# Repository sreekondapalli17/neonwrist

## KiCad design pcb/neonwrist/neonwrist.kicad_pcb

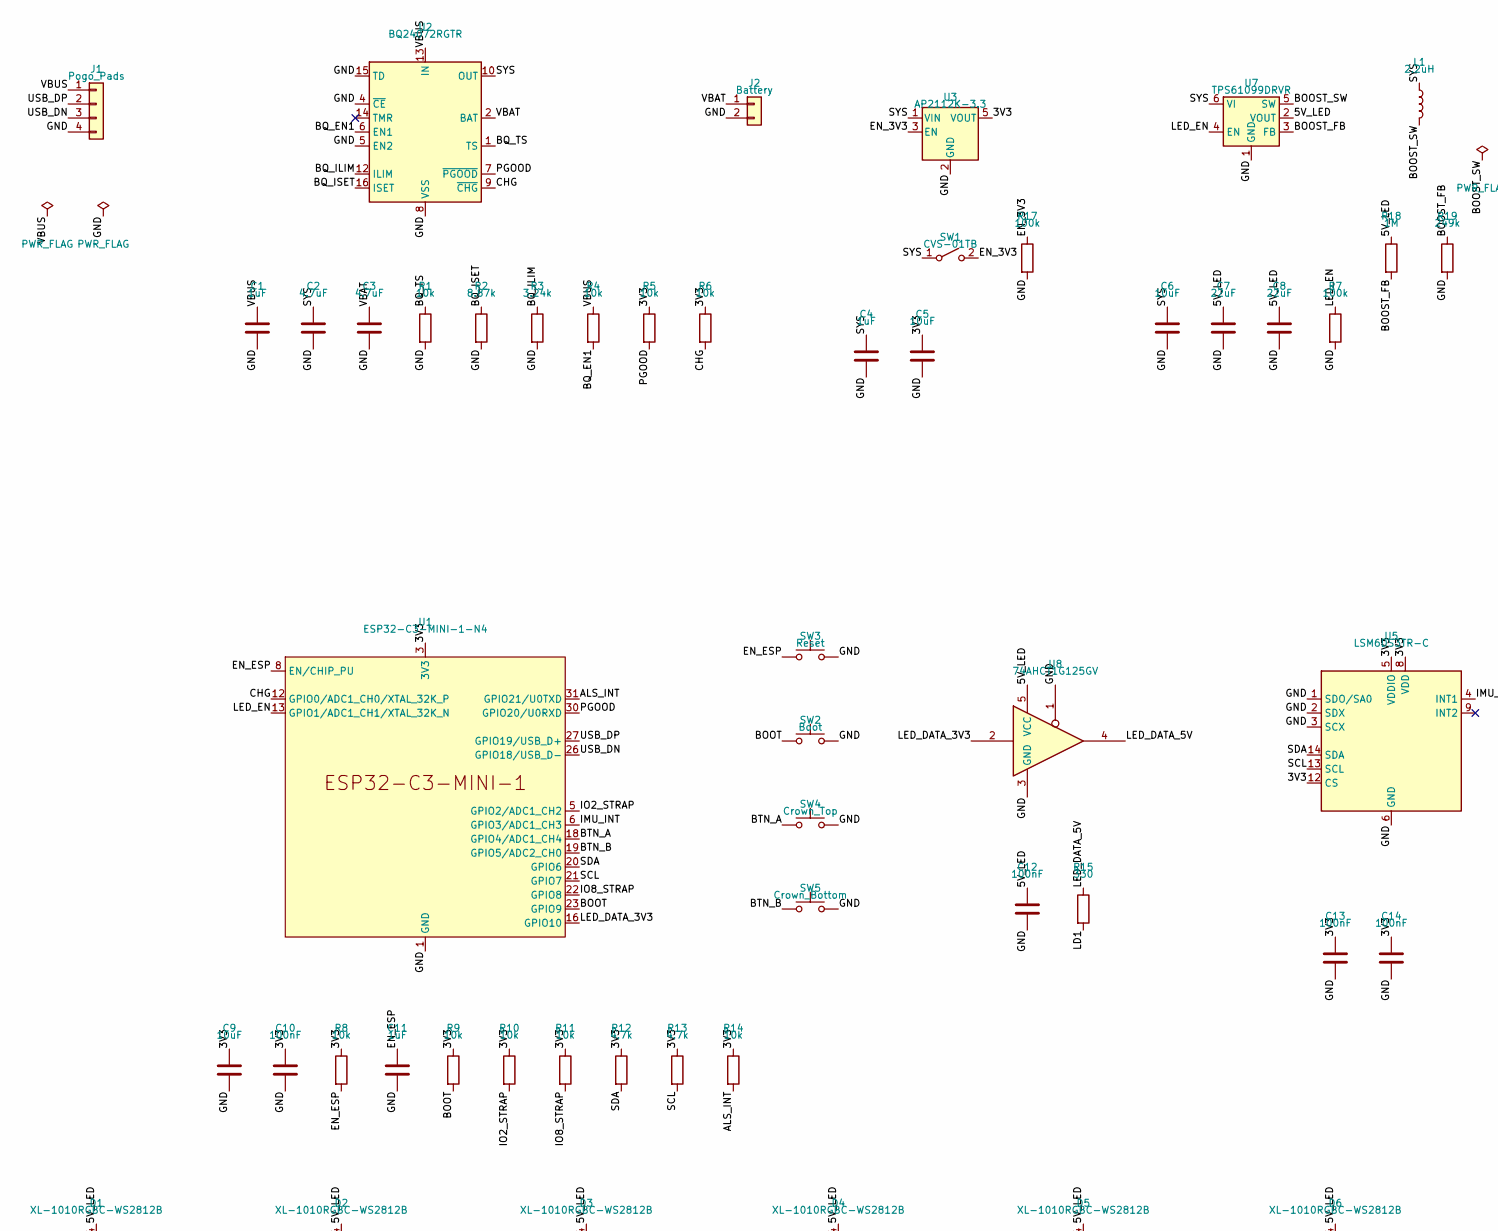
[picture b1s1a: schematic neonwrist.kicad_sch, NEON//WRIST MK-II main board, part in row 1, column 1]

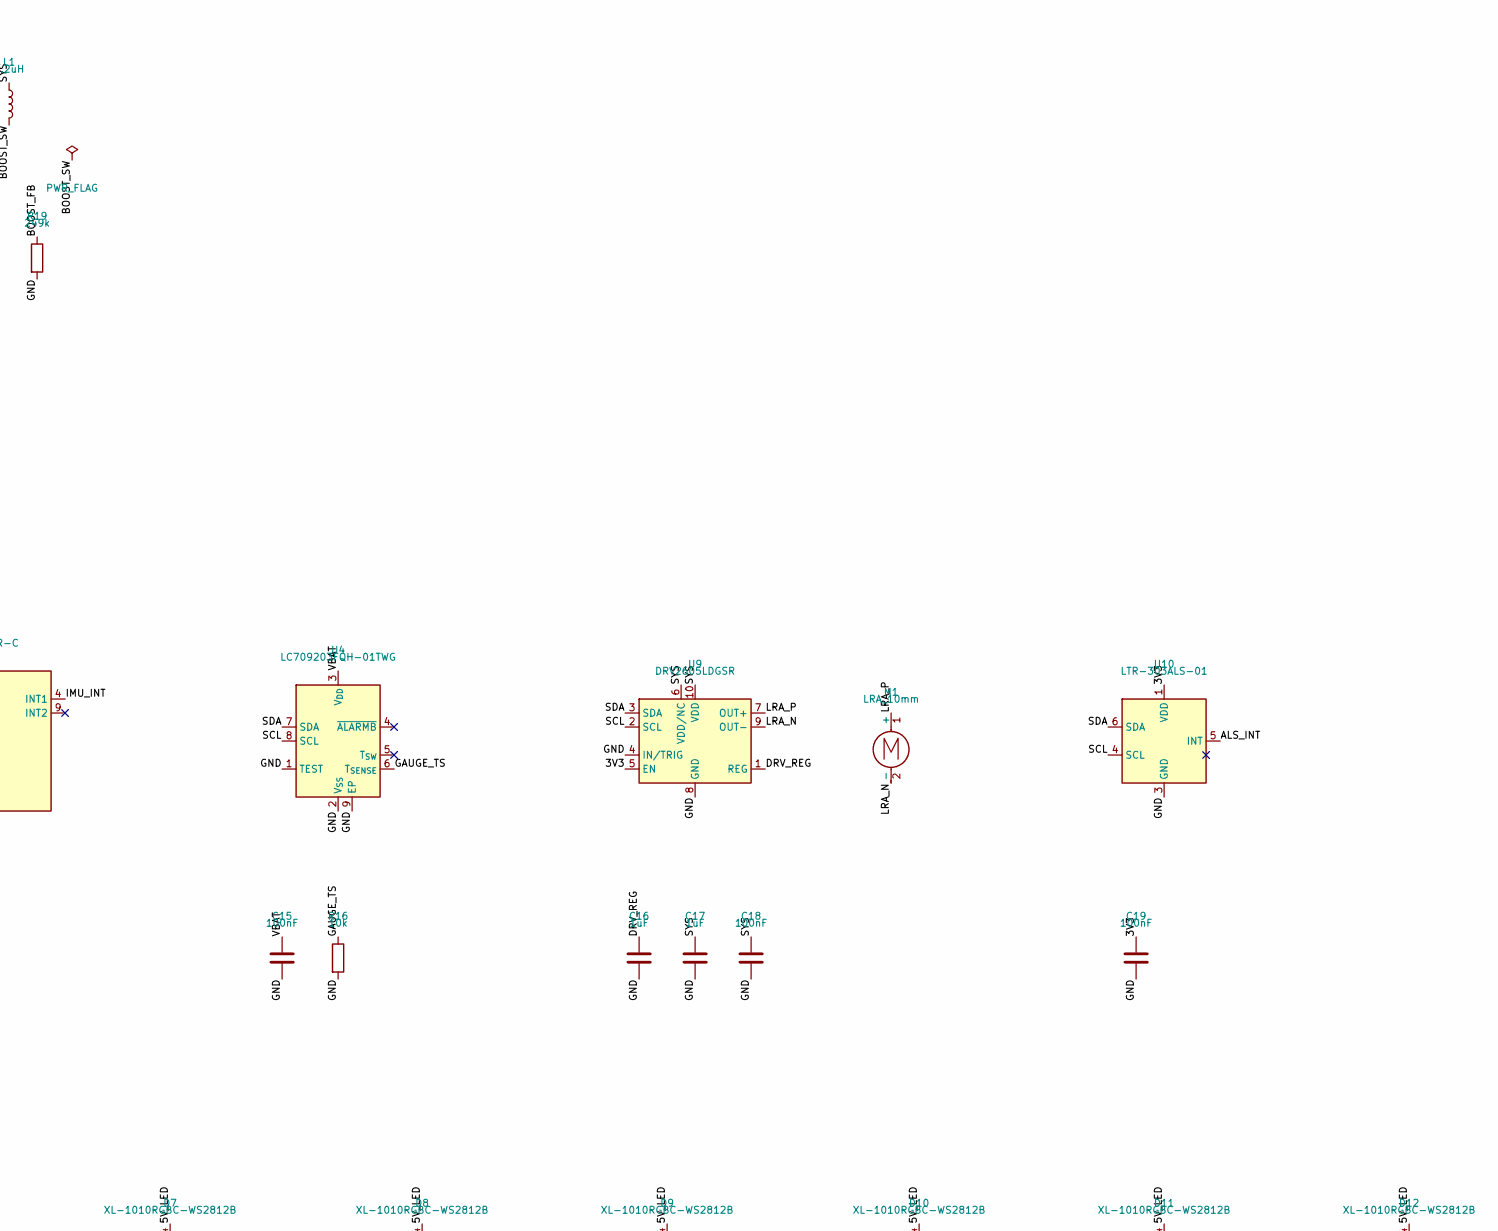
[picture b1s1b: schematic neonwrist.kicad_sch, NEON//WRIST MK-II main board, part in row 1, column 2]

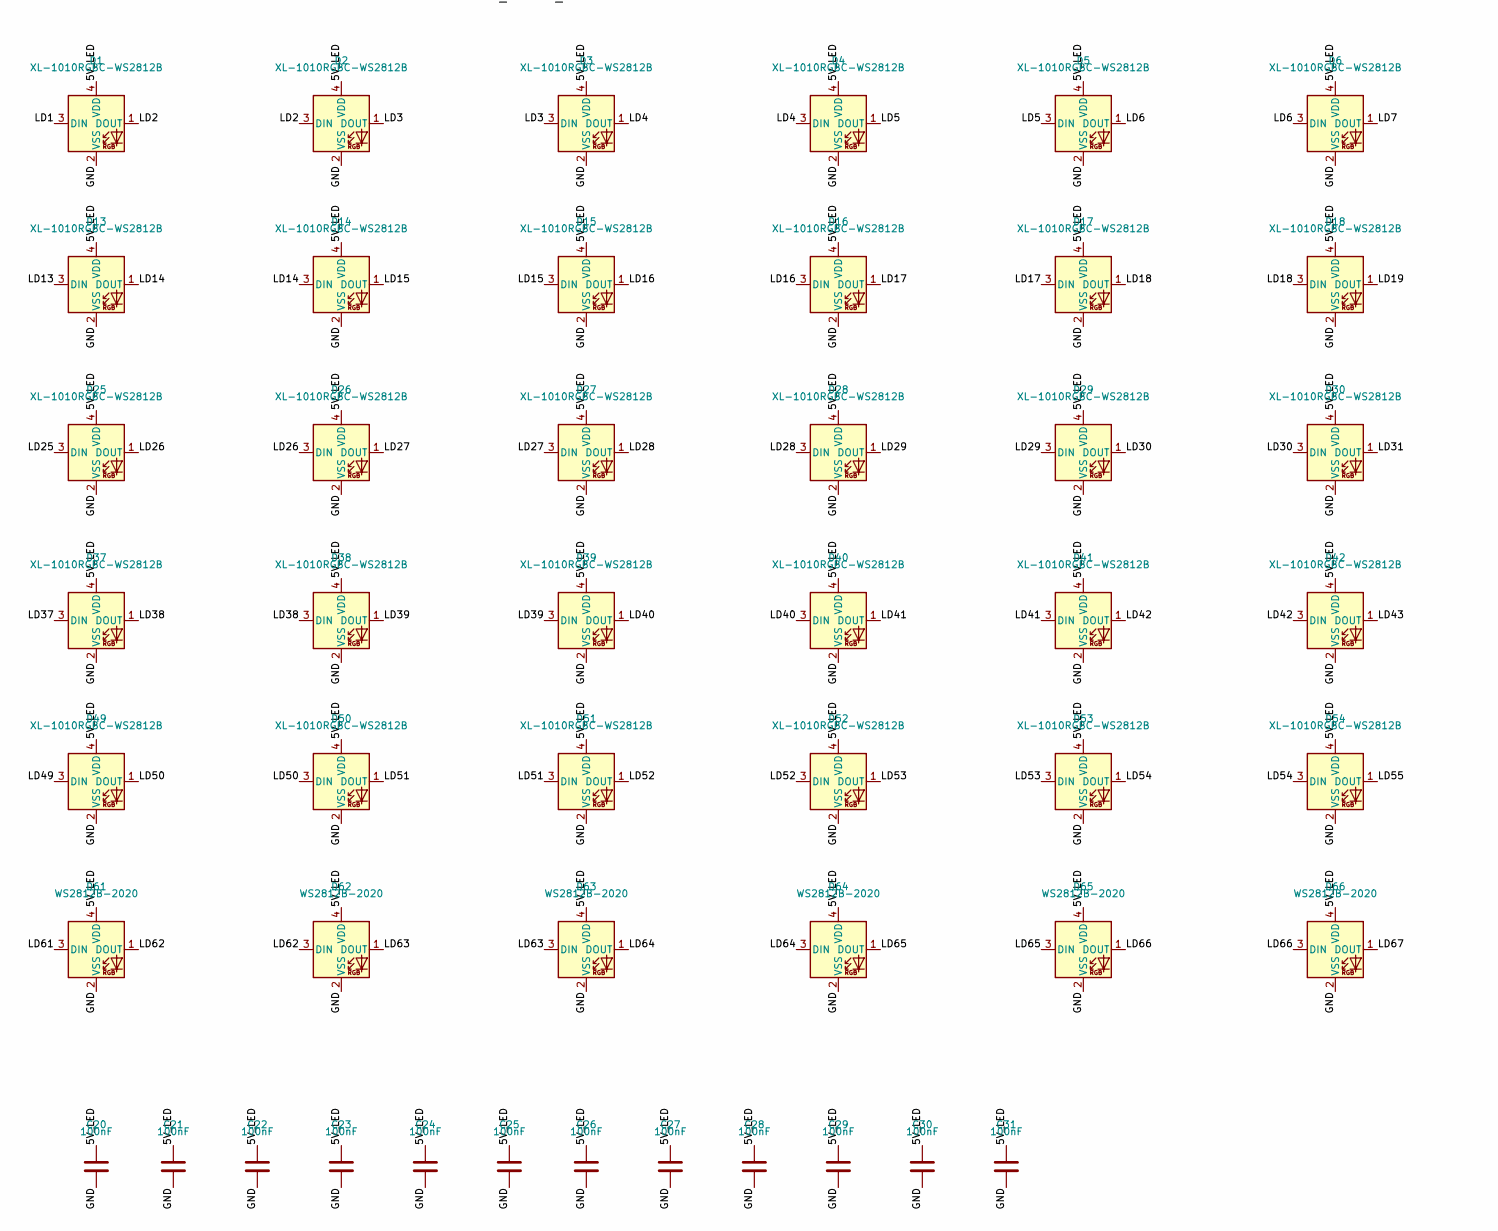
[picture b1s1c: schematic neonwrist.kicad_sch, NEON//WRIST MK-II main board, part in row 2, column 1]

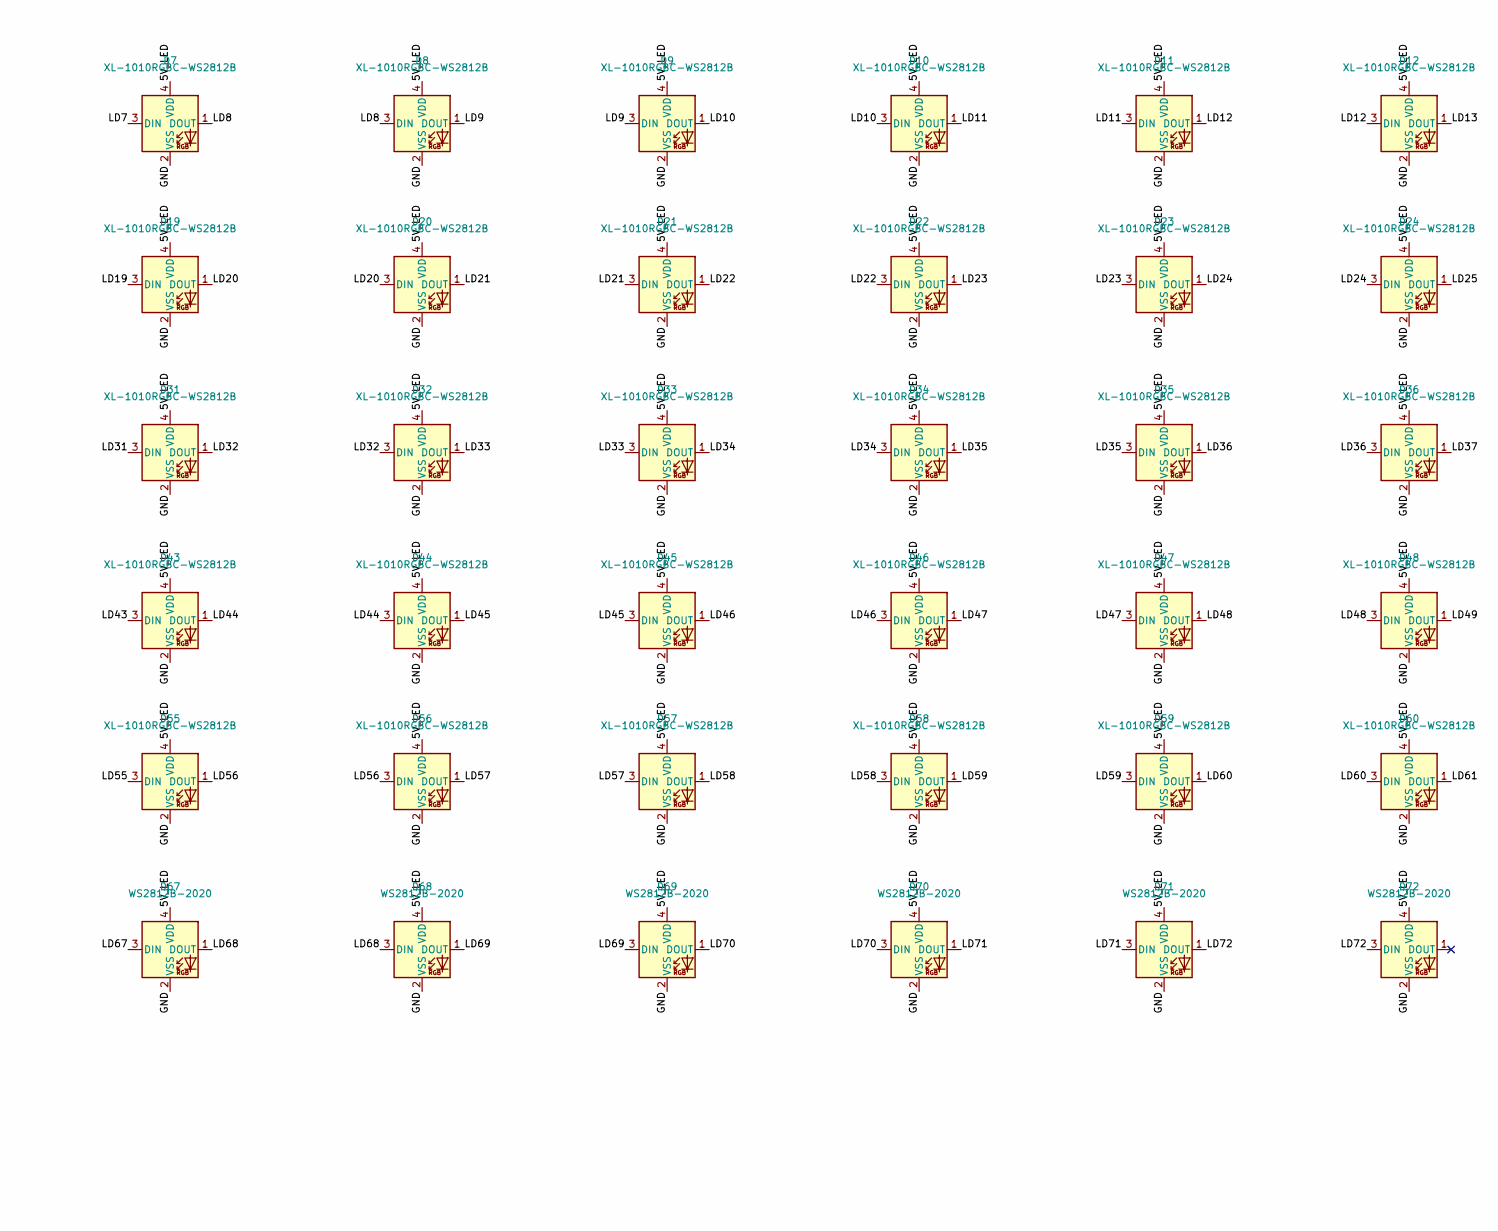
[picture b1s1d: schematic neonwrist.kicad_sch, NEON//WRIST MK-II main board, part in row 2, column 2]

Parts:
C1, C4, C11, C16, C17: 1uF; C_0402_1005Metric
C2, C3: 4.7uF; C_0603_1608Metric
C5, C6, C9: 10uF; C_0603_1608Metric
C7, C8: 22uF; C_0603_1608Metric
C10, C12, C13, C14, C15, C18, C19, C20, C21, C22, C23, C24, C25, C26, C27, C28, C29, C30, C31: 100nF; C_0402_1005Metric
D1, D2, D3, D4, D5, D6, D7, D8, D9, D10, D11, D12, D13, D14, D15, D16, D17, D18, D19, D20, D21, D22, D23, D24, D25, D26, D27, D28, D29, D30, D31, D32, D33, D34, D35, D36, D37, D38, D39, D40, D41, D42, D43, D44, D45, D46, D47, D48, D49, D50, D51, D52, D53, D54, D55, D56, D57, D58, D59, D60: XL-1010RGBC-WS2812B; LED_XL-1010RGBC_1.0x1.0mm
D61, D62, D63, D64, D65, D66, D67, D68, D69, D70, D71, D72: WS2812B-2020; LED_WS2812B-2020_PLCC4_2.0x2.0mm
J1: Pogo_Pads; Pogo_4Pad_P2.5mm
J2: Battery; Battery_2Pad
L1: 2.2uH; L_1008_2520Metric
M1: LRA_10mm; LRA_2Pad
R1, R4, R5, R6, R8, R9, R10, R11, R14, R16: 10k; R_0402_1005Metric
R2: 8.87k; R_0402_1005Metric
R3: 3.24k; R_0402_1005Metric
R7, R17: 100k; R_0402_1005Metric
R12, R13: 4.7k; R_0402_1005Metric
R15: 330; R_0402_1005Metric
R18: 1M; R_0402_1005Metric
R19: 249k; R_0402_1005Metric
SW1: CVS-01TB; SW_DIP_SPSTx01_Slide_Copal_CVS-01xB_W5.9mm_P1mm
SW2: Boot; Panasonic_EVQPUJ_EVQPUA
SW3: Reset; Panasonic_EVQPUJ_EVQPUA
SW4: Crown_Top; Panasonic_EVQPUJ_EVQPUA
SW5: Crown_Bottom; Panasonic_EVQPUJ_EVQPUA
U1: ESP32-C3-MINI-1-N4; ESP32-C3-MINI-1
U2: BQ24072RGTR; VQFN-16-1EP_3x3mm_P0.5mm_EP1.6x1.6mm
U3: AP2112K-3.3; SOT-23-5
U4: LC709203FQH-01TWG; WDFN-8-1EP_4x3mm_P0.65mm_EP2.4x1.8mm
U5: LSM6DS3TR-C; LGA-14_3x2.5mm_P0.5mm_LayoutBorder3x4y
U7: TPS61099DRVR; WSON-6-1EP_2x2mm_P0.65mm_EP1x1.6mm
U8: 74AHCT1G125GV; SOT-23-5
U9: DRV2605LDGSR; MSOP-10_3x3mm_P0.5mm
U10: LTR-303ALS-01; Lite-On_LTR-303ALS-01

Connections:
/3V3: C5.1, C9.1, C10.1, C13.1, C14.1, C19.1, R5.1, R6.1, R8.1, R9.1, R10.1, R11.1, R12.1, R13.1, R14.1, U1.3 (3V3), U3.5 (VOUT), U5.5 (VDDIO), U5.8 (VDD), U5.12 (CS), U9.5 (EN), U10.1 (VDD)
/5V_LED: C7.1, C8.1, C12.1, C20.1, C21.1, C22.1, C23.1, C24.1, C25.1, C26.1, C27.1, C28.1, C29.1, C30.1, C31.1, D1.4 (VDD), D2.4 (VDD), D3.4 (VDD), D4.4 (VDD), D5.4 (VDD), D6.4 (VDD), D7.4 (VDD), D8.4 (VDD), D9.4 (VDD), D10.4 (VDD), D11.4 (VDD), D12.4 (VDD), D13.4 (VDD), D14.4 (VDD), D15.4 (VDD), D16.4 (VDD), D17.4 (VDD), D18.4 (VDD), D19.4 (VDD), D20.4 (VDD), D21.4 (VDD), D22.4 (VDD), D23.4 (VDD), D24.4 (VDD), D25.4 (VDD), D26.4 (VDD), D27.4 (VDD), D28.4 (VDD), D29.4 (VDD), D30.4 (VDD), D31.4 (VDD), D32.4 (VDD), D33.4 (VDD), D34.4 (VDD), D35.4 (VDD), D36.4 (VDD), D37.4 (VDD), D38.4 (VDD), D39.4 (VDD), D40.4 (VDD), D41.4 (VDD), D42.4 (VDD), D43.4 (VDD), D44.4 (VDD), D45.4 (VDD), D46.4 (VDD), D47.4 (VDD), D48.4 (VDD), D49.4 (VDD), D50.4 (VDD), D51.4 (VDD), D52.4 (VDD), D53.4 (VDD), D54.4 (VDD), D55.4 (VDD), D56.4 (VDD), D57.4 (VDD), D58.4 (VDD), D59.4 (VDD), D60.4 (VDD), D61.4 (VDD), D62.4 (VDD), D63.4 (VDD), D64.4 (VDD), D65.4 (VDD), D66.4 (VDD), D67.4 (VDD), D68.4 (VDD), D69.4 (VDD), D70.4 (VDD), D71.4 (VDD), D72.4 (VDD), R18.1, U7.2 (VOUT), U8.5 (VCC)
/ALS_INT: R14.2, U1.31 (GPIO21/U0TXD), U10.5 (INT)
/BOOST_FB: R18.2, R19.1, U7.3 (FB)
/BOOST_SW: L1.2, U7.5 (SW)
/BOOT: R9.2, SW2.1, U1.23 (GPIO9)
/BQ_EN1: R4.2, U2.6 (EN1)
/BQ_ILIM: R3.1, U2.12 (ILIM)
/BQ_ISET: R2.1, U2.16 (ISET)
/BQ_TS: R1.1, U2.1 (TS)
/BTN_A: SW4.1, U1.18 (GPIO4/ADC1_CH4)
/BTN_B: SW5.1, U1.19 (GPIO5/ADC2_CH0)
/CHG: R6.2, U1.12 (GPIO0/ADC1_CH0/XTAL_32K_P), U2.9 (~CHG)
/DRV_REG: C16.1, U9.1 (REG)
/EN_3V3: R17.1, SW1.2 (B), U3.3 (EN)
/EN_ESP: C11.1, R8.2, SW3.1, U1.8 (EN/CHIP_PU)
/GAUGE_TS: R16.1, U4.6 (T_{SENSE})
/GND: C1.2, C2.2, C3.2, C4.2, C5.2, C6.2, C7.2, C8.2, C9.2, C10.2, C11.2, C12.2, C13.2, C14.2, C15.2, C16.2, C17.2, C18.2, C19.2, C20.2, C21.2, C22.2, C23.2, C24.2, C25.2, C26.2, C27.2, C28.2, C29.2, C30.2, C31.2, D1.2 (VSS), D2.2 (VSS), D3.2 (VSS), D4.2 (VSS), D5.2 (VSS), D6.2 (VSS), D7.2 (VSS), D8.2 (VSS), D9.2 (VSS), D10.2 (VSS), D11.2 (VSS), D12.2 (VSS), D13.2 (VSS), D14.2 (VSS), D15.2 (VSS), D16.2 (VSS), D17.2 (VSS), D18.2 (VSS), D19.2 (VSS), D20.2 (VSS), D21.2 (VSS), D22.2 (VSS), D23.2 (VSS), D24.2 (VSS), D25.2 (VSS), D26.2 (VSS), D27.2 (VSS), D28.2 (VSS), D29.2 (VSS), D30.2 (VSS), D31.2 (VSS), D32.2 (VSS), D33.2 (VSS), D34.2 (VSS), D35.2 (VSS), D36.2 (VSS), D37.2 (VSS), D38.2 (VSS), D39.2 (VSS), D40.2 (VSS), D41.2 (VSS), D42.2 (VSS), D43.2 (VSS), D44.2 (VSS), D45.2 (VSS), D46.2 (VSS), D47.2 (VSS), D48.2 (VSS), D49.2 (VSS), D50.2 (VSS), D51.2 (VSS), D52.2 (VSS), D53.2 (VSS), D54.2 (VSS), D55.2 (VSS), D56.2 (VSS), D57.2 (VSS), D58.2 (VSS), D59.2 (VSS), D60.2 (VSS), D61.2 (VSS), D62.2 (VSS), D63.2 (VSS), D64.2 (VSS), D65.2 (VSS), D66.2 (VSS), D67.2 (VSS), D68.2 (VSS), D69.2 (VSS), D70.2 (VSS), D71.2 (VSS), D72.2 (VSS), J1.4, J2.2, R1.2, R2.2, R3.2, R7.2, R16.2, R17.2, R19.2, SW2.2, SW3.2, SW4.2, SW5.2, U1.1 (GND), U1.2 (GND), U1.11 (GND), U1.14 (GND), U1.36 (GND), U1.37 (GND), U1.38 (GND), U1.39 (GND), U1.40 (GND), U1.41 (GND), U1.42 (GND), U1.43 (GND), U1.44 (GND), U1.45 (GND), U1.46 (GND), U1.47 (GND), U1.48 (GND), U1.49 (GND), U1.50 (GND), U1.51 (GND), U1.52 (GND), U1.53 (GND), U2.4 (~CE), U2.5 (EN2), U2.8 (VSS), U2.15 (TD), U2.17 (VSS), U3.2 (GND), U4.1 (TEST), U4.2 (V_{SS}), U4.9 (EP), U5.1 (SDO/SA0), U5.2 (SDX), U5.3 (SCX), U5.6 (GND), U5.7 (GND), U7.1 (GND), U7.7 (GND), U8.1, U8.3 (GND), U9.4 (IN/TRIG), U9.8 (GND), U10.3 (GND)
/IMU_INT: U1.6 (GPIO3/ADC1_CH3), U5.4 (INT1)
/IO2_STRAP: R10.2, U1.5 (GPIO2/ADC1_CH2)
/IO8_STRAP: R11.2, U1.22 (GPIO8)
/LD1: D1.3 (DIN), R15.2
/LD2: D1.1 (DOUT), D2.3 (DIN)
/LD3: D2.1 (DOUT), D3.3 (DIN)
/LD4: D3.1 (DOUT), D4.3 (DIN)
/LD5: D4.1 (DOUT), D5.3 (DIN)
/LD6: D5.1 (DOUT), D6.3 (DIN)
/LD7: D6.1 (DOUT), D7.3 (DIN)
/LD8: D7.1 (DOUT), D8.3 (DIN)
/LD9: D8.1 (DOUT), D9.3 (DIN)
/LD10: D9.1 (DOUT), D10.3 (DIN)
/LD11: D10.1 (DOUT), D11.3 (DIN)
/LD12: D11.1 (DOUT), D12.3 (DIN)
/LD13: D12.1 (DOUT), D13.3 (DIN)
/LD14: D13.1 (DOUT), D14.3 (DIN)
/LD15: D14.1 (DOUT), D15.3 (DIN)
/LD16: D15.1 (DOUT), D16.3 (DIN)
/LD17: D16.1 (DOUT), D17.3 (DIN)
/LD18: D17.1 (DOUT), D18.3 (DIN)
/LD19: D18.1 (DOUT), D19.3 (DIN)
/LD20: D19.1 (DOUT), D20.3 (DIN)
/LD21: D20.1 (DOUT), D21.3 (DIN)
/LD22: D21.1 (DOUT), D22.3 (DIN)
/LD23: D22.1 (DOUT), D23.3 (DIN)
/LD24: D23.1 (DOUT), D24.3 (DIN)
/LD25: D24.1 (DOUT), D25.3 (DIN)
/LD26: D25.1 (DOUT), D26.3 (DIN)
/LD27: D26.1 (DOUT), D27.3 (DIN)
/LD28: D27.1 (DOUT), D28.3 (DIN)
/LD29: D28.1 (DOUT), D29.3 (DIN)
/LD30: D29.1 (DOUT), D30.3 (DIN)
/LD31: D30.1 (DOUT), D31.3 (DIN)
/LD32: D31.1 (DOUT), D32.3 (DIN)
/LD33: D32.1 (DOUT), D33.3 (DIN)
/LD34: D33.1 (DOUT), D34.3 (DIN)
/LD35: D34.1 (DOUT), D35.3 (DIN)
/LD36: D35.1 (DOUT), D36.3 (DIN)
/LD37: D36.1 (DOUT), D37.3 (DIN)
/LD38: D37.1 (DOUT), D38.3 (DIN)
/LD39: D38.1 (DOUT), D39.3 (DIN)
/LD40: D39.1 (DOUT), D40.3 (DIN)
/LD41: D40.1 (DOUT), D41.3 (DIN)
/LD42: D41.1 (DOUT), D42.3 (DIN)
/LD43: D42.1 (DOUT), D43.3 (DIN)
/LD44: D43.1 (DOUT), D44.3 (DIN)
/LD45: D44.1 (DOUT), D45.3 (DIN)
/LD46: D45.1 (DOUT), D46.3 (DIN)
/LD47: D46.1 (DOUT), D47.3 (DIN)
/LD48: D47.1 (DOUT), D48.3 (DIN)
/LD49: D48.1 (DOUT), D49.3 (DIN)
/LD50: D49.1 (DOUT), D50.3 (DIN)
/LD51: D50.1 (DOUT), D51.3 (DIN)
/LD52: D51.1 (DOUT), D52.3 (DIN)
/LD53: D52.1 (DOUT), D53.3 (DIN)
/LD54: D53.1 (DOUT), D54.3 (DIN)
/LD55: D54.1 (DOUT), D55.3 (DIN)
/LD56: D55.1 (DOUT), D56.3 (DIN)
/LD57: D56.1 (DOUT), D57.3 (DIN)
/LD58: D57.1 (DOUT), D58.3 (DIN)
/LD59: D58.1 (DOUT), D59.3 (DIN)
/LD60: D59.1 (DOUT), D60.3 (DIN)
/LD61: D60.1 (DOUT), D61.3 (DIN)
/LD62: D61.1 (DOUT), D62.3 (DIN)
/LD63: D62.1 (DOUT), D63.3 (DIN)
/LD64: D63.1 (DOUT), D64.3 (DIN)
/LD65: D64.1 (DOUT), D65.3 (DIN)
/LD66: D65.1 (DOUT), D66.3 (DIN)
/LD67: D66.1 (DOUT), D67.3 (DIN)
/LD68: D67.1 (DOUT), D68.3 (DIN)
/LD69: D68.1 (DOUT), D69.3 (DIN)
/LD70: D69.1 (DOUT), D70.3 (DIN)
/LD71: D70.1 (DOUT), D71.3 (DIN)
/LD72: D71.1 (DOUT), D72.3 (DIN)
/LED_DATA_3V3: U1.16 (GPIO10), U8.2
/LED_DATA_5V: R15.1, U8.4
/LED_EN: R7.1, U1.13 (GPIO1/ADC1_CH1/XTAL_32K_N), U7.4 (EN)
/LRA_N: M1.2 (-), U9.9 (OUT-)
/LRA_P: M1.1 (+), U9.7 (OUT+)
/PGOOD: R5.2, U1.30 (GPIO20/U0RXD), U2.7 (~PGOOD)
/SCL: R13.2, U1.21 (GPIO7), U4.8 (SCL), U5.13 (SCL), U9.2 (SCL), U10.4 (SCL)
/SDA: R12.2, U1.20 (GPIO6), U4.7 (SDA), U5.14 (SDA), U9.3 (SDA), U10.6 (SDA)
/SYS: C2.1, C4.1, C6.1, C17.1, C18.1, L1.1, SW1.1 (A), U2.10 (OUT), U2.11 (OUT), U3.1 (VIN), U7.6 (VI), U9.6 (VDD/NC), U9.10 (VDD)
/USB_DN: J1.3, U1.26 (GPIO18/USB_D-)
/USB_DP: J1.2, U1.27 (GPIO19/USB_D+)
/VBAT: C3.1, C15.1, J2.1, U2.2 (BAT), U2.3 (BAT), U4.3 (V_{DD})
/VBUS: C1.1, J1.1, R4.1, U2.13 (IN)

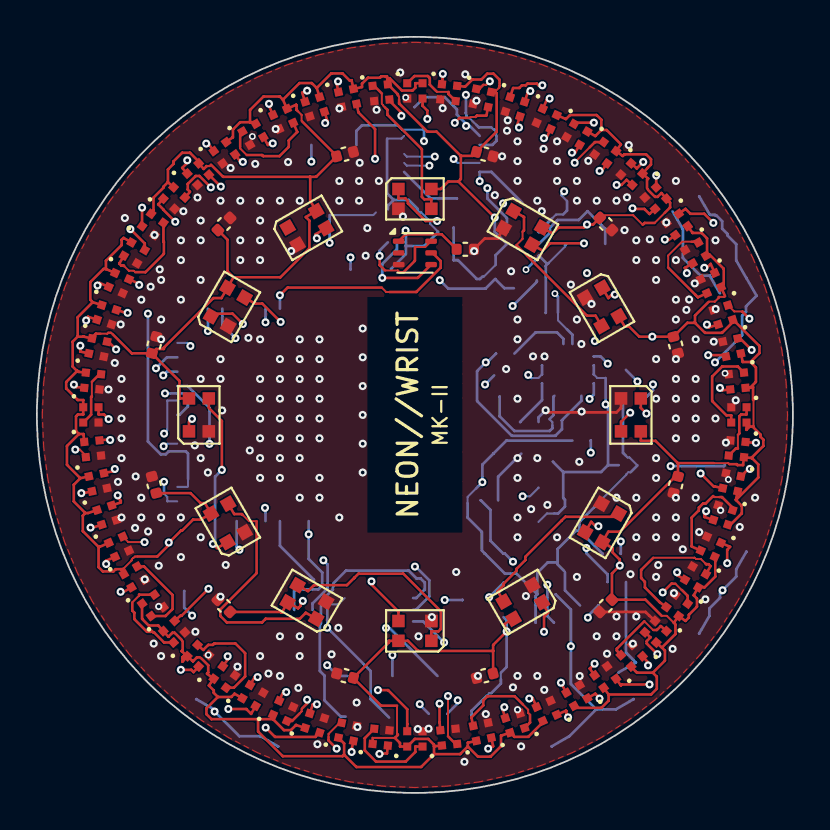
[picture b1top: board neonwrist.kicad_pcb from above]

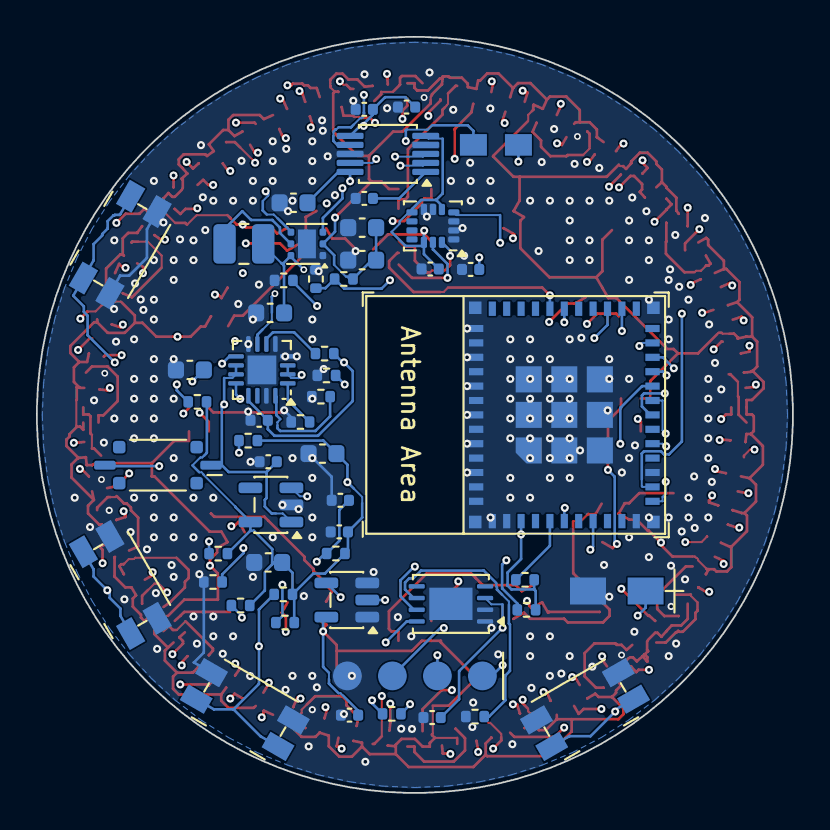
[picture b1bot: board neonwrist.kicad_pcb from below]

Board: 4 copper layers, 42.0 x 42.0 mm, 140 parts (54 on the bottom side), 106 nets.

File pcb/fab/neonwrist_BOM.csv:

Comment,Designator,Footprint,LCSC Part #
XL-1010RGBC-WS2812B,"D1,D2,D3,D4,D5,D6,D7,D8,D9,D10,D11,D12,D13,D14,D15,D16,D17,D18,D19,D20,D21,D22,D23,D24,D25,D26,D27,D28,D29,D30,D31,D32,D33,D34,D35,D36,D37,D38,D39,D40,D41,D42,D43,D44,D45,D46,D47,D48,D49,D50,D51,D52,D53,D54,D55,D56,D57,D58,D59,D60",LED_XL-1010RGBC_1.0x1.0mm,C5349953
100nF,"C10,C12,C13,C14,C15,C18,C19,C20,C21,C22,C23,C24,C25,C26,C27,C28,C29,C30,C31",C_0402_1005Metric,C1525
LTR-303ALS-01,U10,Lite-On_LTR-303ALS-01,C364577
WS2812B-2020,"D61,D62,D63,D64,D65,D66,D67,D68,D69,D70,D71,D72",LED_WS2812B-2020_PLCC4_2.0x2.0mm,C965555
EVQ-PUA02K,"SW2,SW3,SW4,SW5",Panasonic_EVQPUJ_EVQPUA,C128539
LSM6DS3TR-C,U5,LGA-14_3x2.5mm_P0.5mm_LayoutBorder3x4y,C967633
TPS61099DRVR,U7,WSON-6-1EP_2x2mm_P0.65mm_EP1x1.6mm,C2842395
4.7k,"R12,R13",R_0402_1005Metric,C25900
AP2112K-3.3,U3,SOT-23-5,C51118
3.24k,R3,R_0402_1005Metric,C11457
1uF,"C1,C4,C11,C16,C17",C_0402_1005Metric,C52923
DRV2605LDGSR,U9,MSOP-10_3x3mm_P0.5mm,C527464
10uF,"C5,C6,C9",C_0603_1608Metric,C19702
100k,"R7,R17",R_0402_1005Metric,C25741
10k,"R1,R4,R5,R6,R8,R9,R10,R11,R14,R16",R_0402_1005Metric,C25744
330,R15,R_0402_1005Metric,C25104
22uF,"C7,C8",C_0603_1608Metric,C59461
4.7uF,"C2,C3",C_0603_1608Metric,C19666
BQ24072RGTR,U2,VQFN-16-1EP_3x3mm_P0.5mm_EP1.6x1.6mm,C140288
LC709203FQH-01TWG,U4,WDFN-8-1EP_4x3mm_P0.65mm_EP2.4x1.8mm,C152311
249k 1% 0402,R19,R_0402_1005Metric,
CVS-01TB,SW1,SW_DIP_SPSTx01_Slide_Copal_CVS-01xB_W5.9mm_P1mm,C2921743
ESP32-C3-MINI-1-N4,U1,ESP32-C3-MINI-1,C2838502
1M,R18,R_0402_1005Metric,C26083
2.2uH 1008 >=1.5A shielded,L1,L_1008_2520Metric,
74AHCT1G125GV,U8,SOT-23-5,C12494
8.87k 1% 0402,R2,R_0402_1005Metric,
